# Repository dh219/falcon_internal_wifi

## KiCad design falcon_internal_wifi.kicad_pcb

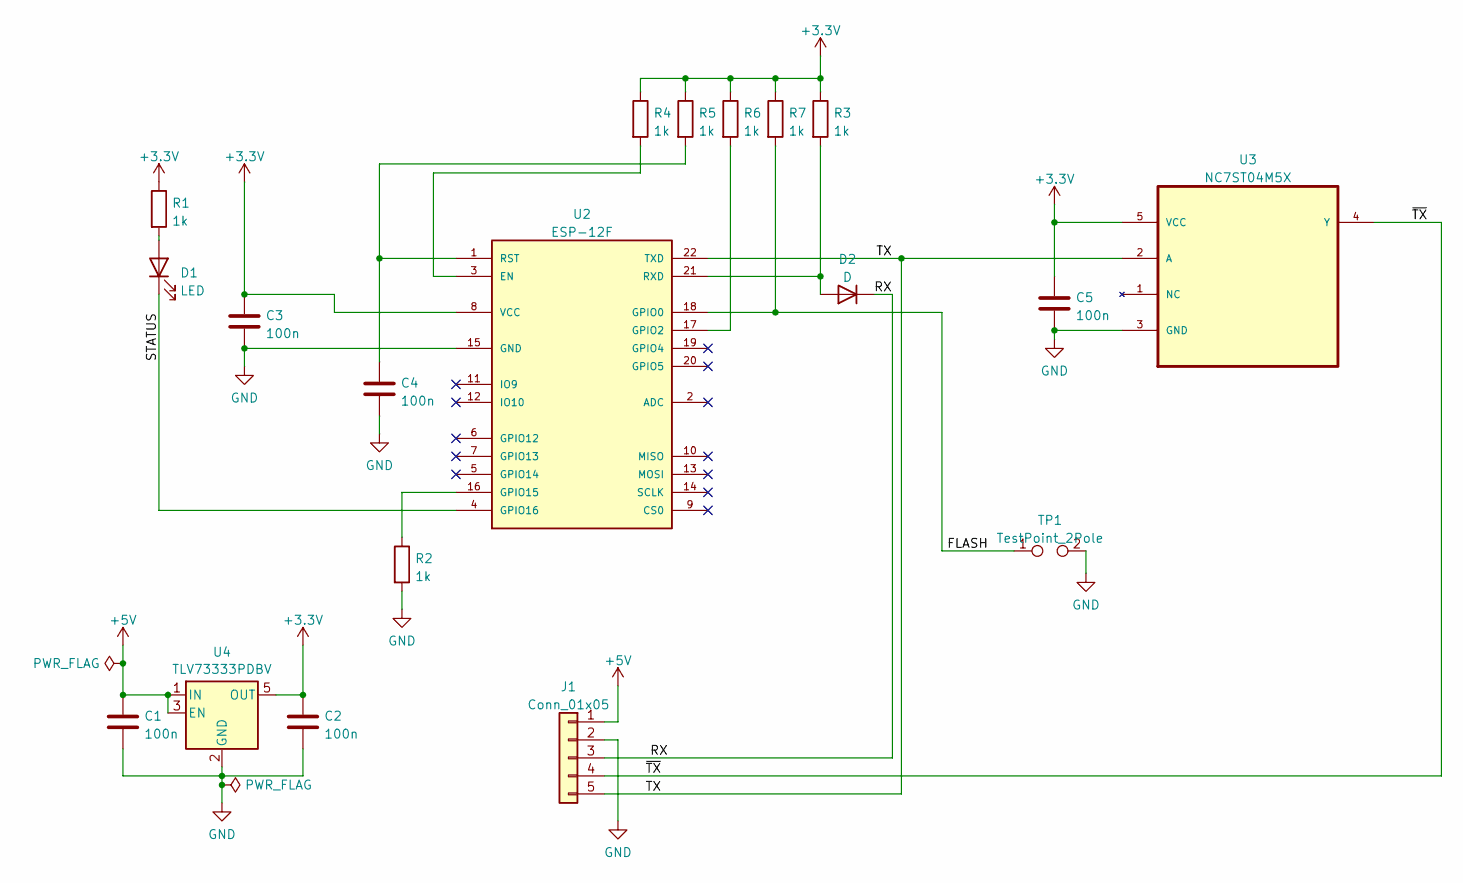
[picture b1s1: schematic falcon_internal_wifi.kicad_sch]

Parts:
C1, C2, C3, C4, C5: 100n; C_0603_1608Metric
D1: LED; LED_0805_2012Metric
D2: D; D_0805_2012Metric
J1: Conn_01x05; SolderWire-0.5sqmm_1x05_P4.6mm_D0.9mm_OD2.1mm
R1, R2, R3, R4, R5, R6, R7: 1k; R_0603_1608Metric
TP1: TestPoint_2Pole; SolderJumper-2_P1.3mm_Open_RoundedPad1.0x1.5mm
U2: ESP-12F
U3: NC7ST04M5X; SOT95P280X145-5N; MPN NC7ST04M5X
U4: TLV73333PDBV; SOT-23-5

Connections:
+3.3V: C2.1, C3.1, C5.1, R1.1, R3.1, R4.1, R5.1, R6.1, R7.1, U2.8 (VCC), U3.5 (VCC), U4.5 (OUT)
+5V: C1.1, J1.1, U4.1 (IN), U4.3 (EN)
/FLASH: R7.2, TP1.1, U2.18 (GPIO0)
/RX: D2.1 (K), J1.3
/STATUS: D1.1 (K), U2.4 (GPIO16)
/TX: J1.5, U2.22 (TXD), U3.2 (A)
/~TX: J1.4, U3.4 (Y)
GND: C1.2, C2.2, C3.2, C4.2, C5.2, J1.2, R2.2, TP1.2, U2.15 (GND), U3.3 (GND), U4.2 (GND)
unnamed: D1.2 (A), R1.2
unnamed: D2.2 (A), R3.2, U2.21 (RXD)
unnamed: R4.2, U2.3 (EN)
unnamed: R6.2, U2.17 (GPIO2)
unnamed: R2.1, U2.16 (GPIO15)
unnamed: C4.1, R5.2, U2.1 (RST)

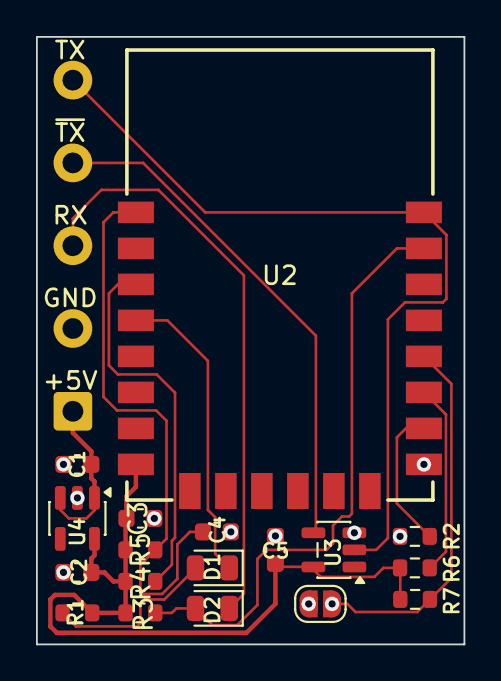
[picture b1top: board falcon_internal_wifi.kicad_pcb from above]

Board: 2 copper layers, 23.8 x 33.7 mm, 19 parts (0 on the bottom side), 14 nets.

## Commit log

2025-11-04 First import of nascent internal wifi board with 0805 components.
2025-11-10 Second design with smaller passive
2025-11-10 Version as quoted. Considering just going back to 0805.
2025-11-25 Version 1 as ordered
2025-11-25 Added manufacturing files as ordered for rev 1

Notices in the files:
falcon_internal_wifi.kicad_pcb:
Copyright D Henderson 2025
